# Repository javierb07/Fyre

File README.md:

# Fyre Smartwatch in Development
Smartwatch designed during Summer 2020 at Purdue Milestones

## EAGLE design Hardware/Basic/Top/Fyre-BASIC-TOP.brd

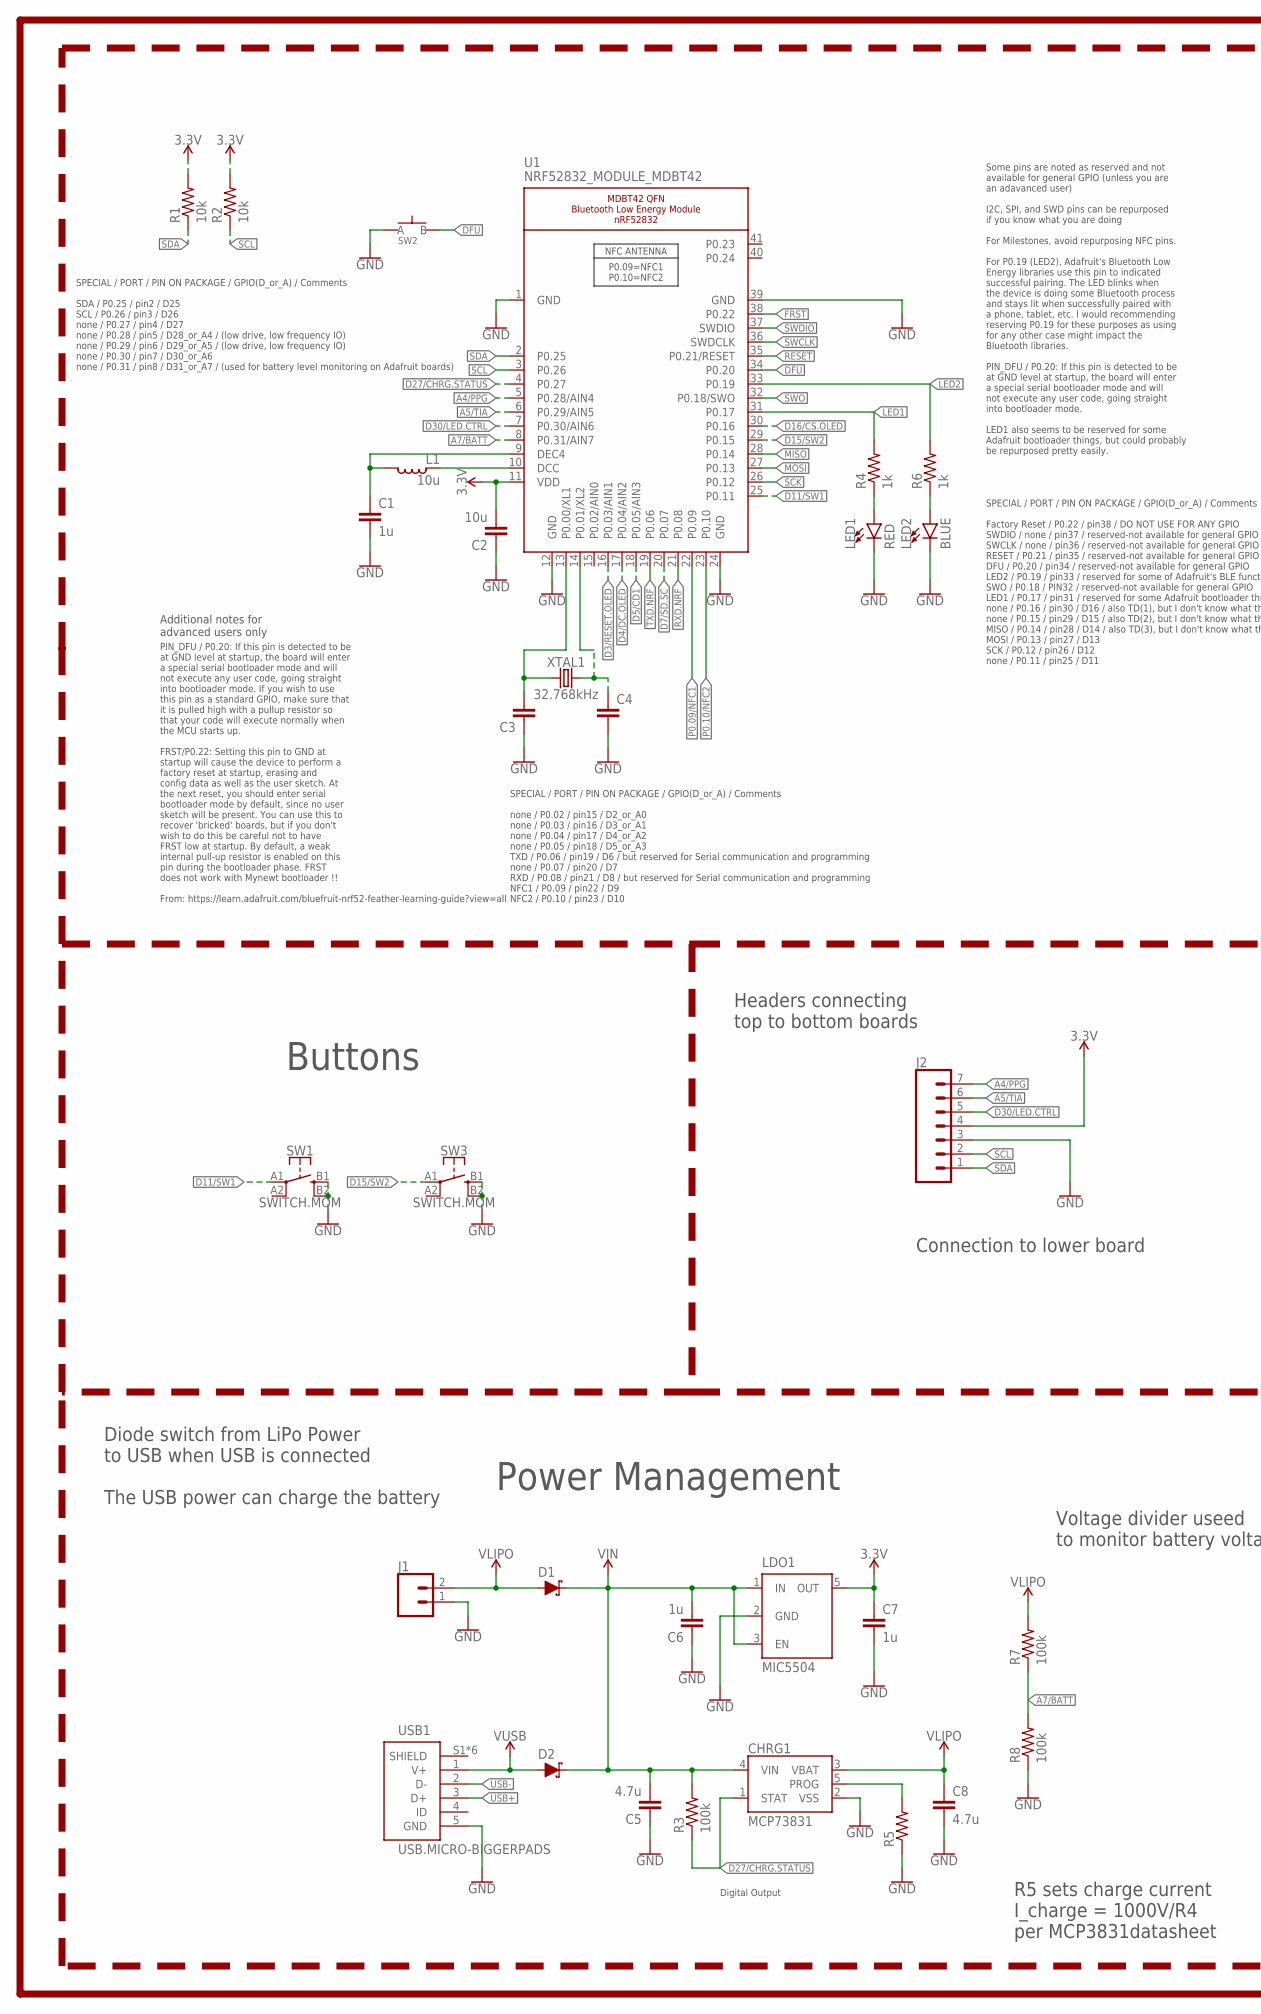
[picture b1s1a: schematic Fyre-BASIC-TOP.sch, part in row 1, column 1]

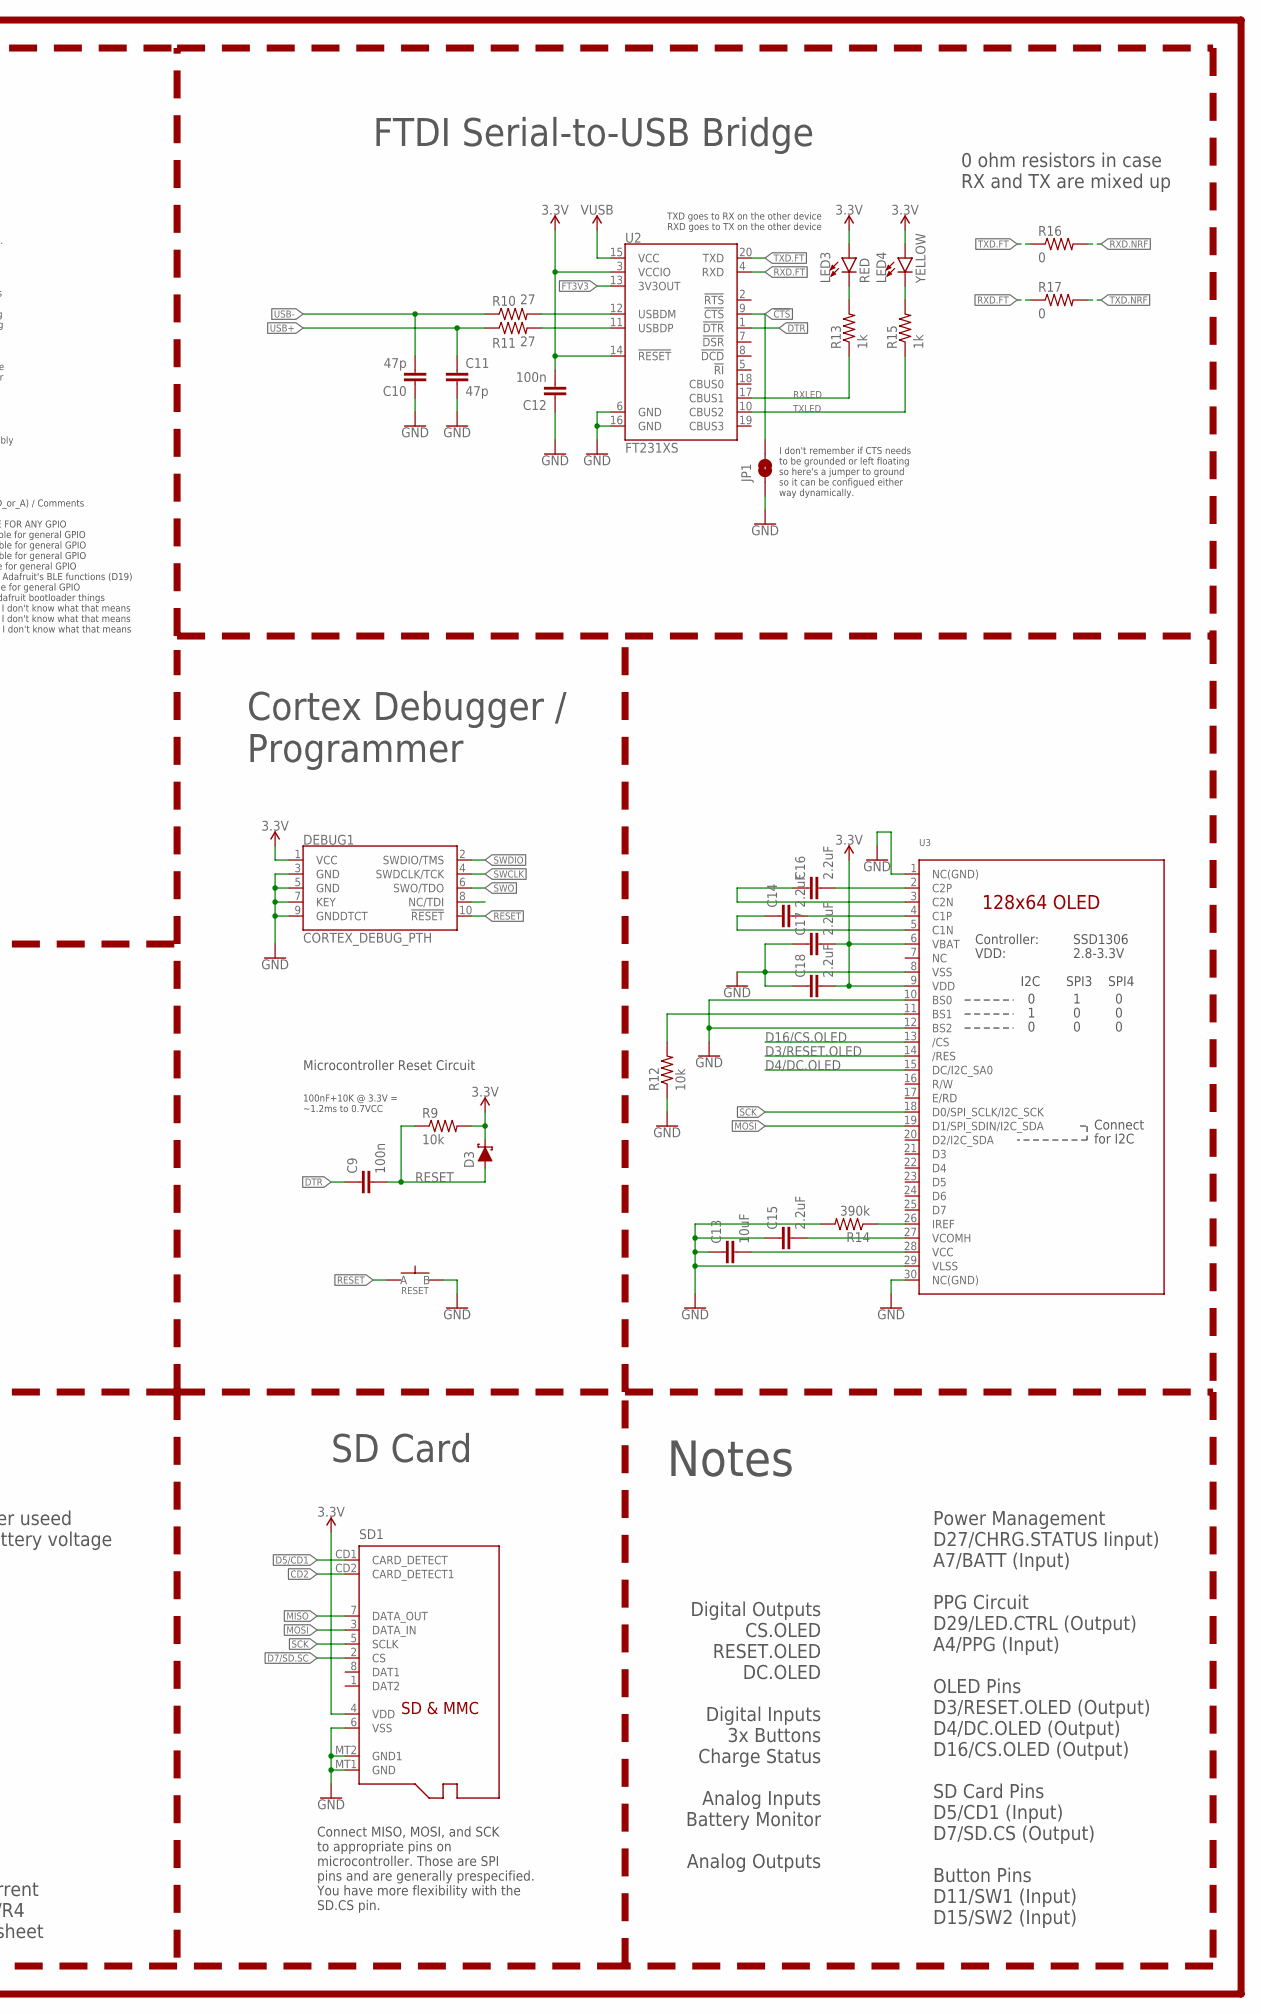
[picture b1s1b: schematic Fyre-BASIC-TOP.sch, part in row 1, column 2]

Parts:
C1, C6, C7: 1u; C0603
C2: 10u; C0805
C3, C4: CAPACITOR0603; C0603
C5, C8: 4.7u; C0603
C9, C12: 100n; C0603
C10, C11: 47p; C0603
C13: 10uF; C0603
C14, C15, C16, C17, C18: 2.2uF; C0402
CHRG1: MCP73831; SOT23-5
D1, D2, D3: SCHOTTKY-USC; USC
DEBUG1: CORTEX_DEBUG_PTH; 2X5-PTH-1.27MM
J1: CONN_02; 1X02
J2: CONN_07-1.27MM; 1X07_1.27MM
JP1: JUMPER-SMT_2_NO_SILK; SMT-JUMPER_2_NO_SILK
L1: 10u; L0603
LDO1: MIC5504; SOT23-5
LED1, LED3: RED; LED-0603
LED2: BLUE; LED-0603
LED4: YELLOW; LED-0603
R1, R2, R9, R12: 10k; R0603
R3, R7, R8: 100k; R0603
R4, R6, R13, R15: 1k; R0603
R5: RESISTOR0603; R0603
R10, R11: 27; R0603
R14: 390k; R0603
R16, R17: 0; R0603
RESET: SPST-PTS830GG140-COPY.1-3; BUTTON-GULLWING
SD1: MICROSD
SW1, SW3: SWITCH.MOM; TACTILE_SWITCH_SMD_6.2MM_TALL
SW2: SPST-PTS830GG140-COPY.1-3; BUTTON-GULLWING
U1: NRF52832_MODULE_MDBT42; BLE_MODULE_RAYTAC_MDBT42
U2: FT231XS; SSOP20_L
U3: DISP_OLED_UG-2864HSWEG01-NO-WRAPAROUND; UG-2864HSWEG01_0.96IN_NO-WRAPAROUND
USB1: USB.MICRO-BIGGERPADS; USB-MICRO-01.BIGGERPADS
XTAL1: 32.768kHz; 2-SMD.NOLEAD.2.0MMTO1.2MM

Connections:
3.3V: C2.2, C7.1, C12.2, C17.2, C18.2, D3.- (C), DEBUG1.1 (VCC), J2.4, LDO1.5 (OUT), LED3.A, LED4.A, R1.2, R2.2, R9.2, SD1.4 (VDD), U1.11 (VDD), U2.3 (VCCIO), U2.14 (!RESET), U3.6 (VBAT), U3.9 (VDD)
!CTS: JP1.2, U2.9 (!CTS)
A4/PPG: J2.7, U1.5 (P0.28/AIN4)
A5/TIA: J2.6, U1.6 (P0.29/AIN5)
A7/BATT: R7.1, R8.2, U1.8 (P0.31/AIN7)
CD2: SD1.CD2 (CARD_DETECT1)
D3/RESET.OLED: U1.16 (P0.03/AIN1), U3.14 (/RES)
D4/DC.OLED: U1.17 (P0.04/AIN2), U3.15 (DC/I2C_SA0)
D5/CD1: SD1.CD1 (CARD_DETECT), U1.18 (P0.05/AIN3)
D7/SD.SC: SD1.2 (CS), U1.20 (P0.07)
D11/SW1: SW1.A1 (1), U1.25 (P0.11)
D15/SW2: SW3.A1 (1), U1.29 (P0.15)
D16/CS.OLED: U1.30 (P0.16), U3.13 (/CS)
D27/CHRG.STATUS: CHRG1.1 (STAT), R3.1, U1.4 (P0.27)
D30/LED.CTRL: J2.5, U1.7 (P0.30/AIN6)
DFU: SW2.3 (B), U1.34 (P0.20)
DTR: C9.1, U2.1 (!DTR)
FRST: U1.38 (P0.22)
FT3V3: U2.13 (3V3OUT)
GND: C1.2, C2.1, C3.1, C4.2, C5.1, C6.1, C7.2, C8.2, C10.1, C11.2, C12.1, C13.1, C15.1, C17.1, C18.1, CHRG1.2 (VSS), DEBUG1.3 (GND), DEBUG1.5 (GND), DEBUG1.7 (KEY), DEBUG1.9 (GNDDTCT), J1.1, J2.3, JP1.1, LDO1.2 (GND), LED1.C, LED2.C, R5.1, R8.1, R12.1, R14.2, RESET.3 (B), SD1.6 (VSS), SD1.MT1 (GND), SD1.MT2 (GND1), SW1.B1 (3), SW1.B2 (4), SW2.1 (A), SW3.B1 (3), SW3.B2 (4), U1.1 (GND), U1.12 (GND), U1.24 (GND), U1.39 (GND), U2.6 (GND), U2.16 (GND), U3.1 (NC(GND)), U3.8 (VSS), U3.10 (BS0), U3.12 (BS2), U3.29 (VLSS), U3.30 (NC(GND)), USB1.5 (GND)
LED1: R4.2, U1.31 (P0.17)
LED2: R6.2, U1.33 (P0.19)
MISO: SD1.7 (DATA_OUT), U1.28 (P0.14)
MOSI: SD1.3 (DATA_IN), U1.27 (P0.13), U3.19 (D1/SPI_SDIN/I2C_SDA)
unnamed: R12.2, U3.11 (BS1)
unnamed: R14.1, U3.26 (IREF)
unnamed: C16.2, U3.2 (C2P)
unnamed: C3.2, U1.13 (P0.00/XL1), XTAL1.P$1 (1)
unnamed: C16.1, U3.3 (C2N)
unnamed: C14.2, U3.4 (C1P)
unnamed: C14.1, U3.5 (C1N)
unnamed: LED1.A, R4.1
unnamed: LED2.A, R6.1
unnamed: L1.1, U1.10 (DCC)
unnamed: C1.1, L1.2, U1.9 (DEC4)
unnamed: C13.2, U3.28 (VCC)
unnamed: C15.2, U3.27 (VCOMH)
unnamed: C4.1, U1.14 (P0.01/XL2), XTAL1.P$2 (2)
unnamed: CHRG1.5 (PROG), R5.2
unnamed: R10.2, U2.12 (USBDM)
unnamed: R11.2, U2.11 (USBDP)
unnamed: LED3.C, R13.2
unnamed: LED4.C, R15.2
P0.09/NFC1: U1.22 (P0.09)
P0.10/NFC2: U1.23 (P0.10)
RESET: C9.2, D3.+ (A), DEBUG1.10 (!RESET), R9.1, RESET.1 (A), U1.35 (P0.21/RESET)
RXD.FT: R17.1, U2.4 (RXD)
RXD.NRF: R16.2, U1.21 (P0.08)
RXLED: R13.1, U2.17 (CBUS1)
SCK: SD1.5 (SCLK), U1.26 (P0.12), U3.18 (D0/SPI_SCLK/I2C_SCK)
SCL: J2.2, R2.1, U1.3 (P0.26)
SDA: J2.1, R1.1, U1.2 (P0.25)
SWCLK: DEBUG1.4 (SWDCLK/TCK), U1.36 (SWDCLK)
SWDIO: DEBUG1.2 (SWDIO/TMS), U1.37 (SWDIO)
SWO: DEBUG1.6 (SWO/TDO), U1.32 (P0.18/SWO)
TXD.FT: R16.1, U2.20 (TXD)
TXD.NRF: R17.2, U1.19 (P0.06)
TXLED: R15.1, U2.10 (CBUS2)
USB+: C11.1, R11.1, USB1.3 (D+)
USB-: C10.2, R10.1, USB1.2 (D-)
VIN: C5.2, C6.2, CHRG1.4 (VIN), D1.- (C), D2.- (C), LDO1.1 (IN), LDO1.3 (EN), R3.2
VLIPO: C8.1, CHRG1.3 (VBAT), D1.+ (A), J1.2, R7.2
V_USB: D2.+ (A), U2.15 (VCC), USB1.1 (V+)

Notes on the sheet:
Microcontroller Reset Circuit
100nF+10K @ 3.3V = ~1.2ms to 0.7VCC
SPECIAL / PORT / PIN ON PACKAGE / GPIO(D_or_A) / Comments SDA / P0.25 / pin2 / D25 SCL / P0.26 / pin3 / D26 none / P0.27 / pin4 / D27 none / P0.28 / pin5 / D28_or_A4 / (low drive, low frequency IO) none / P0.29 / pin6 / D29_or_A5 / (low drive, low frequency IO) none / P0.30 / pin7 / D30_or_A6 none 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
SPECIAL / PORT / PIN ON PACKAGE / GPIO(D_or_A) / Comments none / P0.02 / pin15 / D2_or_A0 none / P0.03 / pin16 / D3_or_A1 none / P0.04 / pin17 / D4_or_A2 none / P0.05 / pin18 / D5_or_A3 TXD / P0.06 / pin19 / D6 / but reserved for Serial communication and programming none / P0.07 / pin20 / D7 RXD / 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
SPECIAL / PORT / PIN ON PACKAGE / GPIO(D_or_A) / Comments Factory Reset / P0.22 / pin38 / DO NOT USE FOR ANY GPIO SWDIO / none / pin37 / reserved-not available for general GPIO SWCLK / none / pin36 / reserved-not available for general GPIO RESET / P0.21 / pin35 / reserved-not available for general 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
Some pins are noted as reserved and not available for general GPIO (unless you are an adavanced user) I2C, SPI, and SWD pins can be repurposed if you know what you are doing For Milestones, avoid repurposing NFC pins. For P0.19 (LED2), Adafruit's Bluetooth Low Energy libraries use this pin to indic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
PIN_DFU / P0.20: If this pin is detected to be at GND level at startup, the board will enter a special serial bootloader mode and will not execute any user code, going straight into bootloader mode. If you wish to use this pin as a standard GPIO, make sure that it is pulled high with a pullup resis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
Additional notes for advanced users only
Connect MISO, MOSI, and SCK to appropriate pins on microcontroller. Those are SPI pins and are generally prespecified. You have more flexibility with the SD.CS pin.
SD Card
Power Management
Buttons
Cortex Debugger / Programmer
Digital Outputs CS.OLED RESET.OLED DC.OLED Digital Inputs 3x Buttons Charge Status Analog Inputs Battery Monitor Analog Outputs
TXD goes to RX on the other device RXD goes to TX on the other device
I don't remember if CTS needs to be grounded or left floating so here's a jumper to ground so it can be configued either way dynamically.
FTDI Serial-to-USB Bridge
Notes
Digital Output
Power Management D27/CHRG.STATUS Iinput) A7/BATT (Input) PPG Circuit D29/LED.CTRL (Output) A4/PPG (Input) OLED Pins D3/RESET.OLED (Output) D4/DC.OLED (Output) D16/CS.OLED (Output) SD Card Pins D5/CD1 (Input) D7/SD.CS (Output) Button Pins D11/SW1 (Input) D15/SW2 (Input)
Connection to lower board
Diode switch from LiPo Power to USB when USB is connected The USB power can charge the battery
R5 sets charge current I_charge = 1000V/R4 per MCP3831datasheet
Voltage divider useed to monitor battery voltage
Headers connecting top to bottom boards
0 ohm resistors in case RX and TX are mixed up

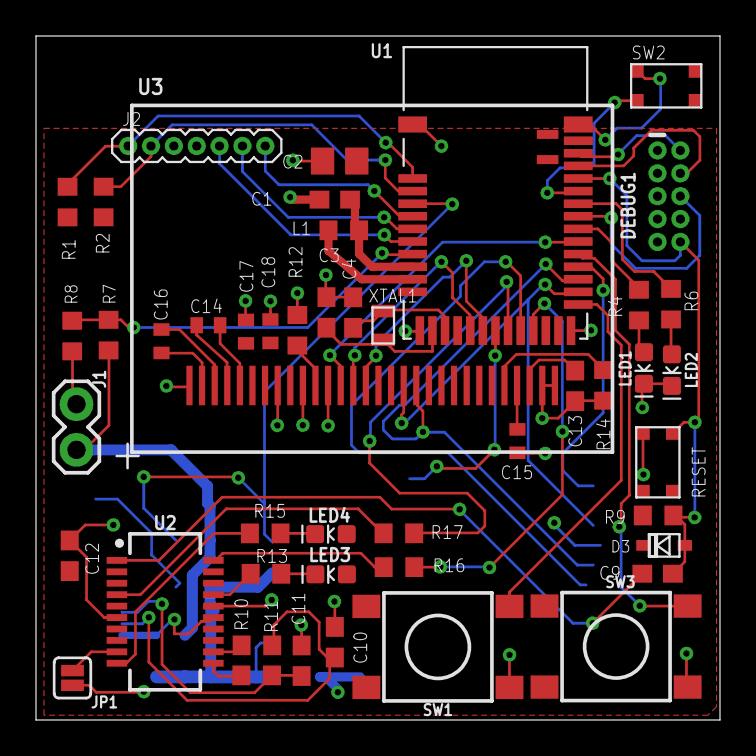
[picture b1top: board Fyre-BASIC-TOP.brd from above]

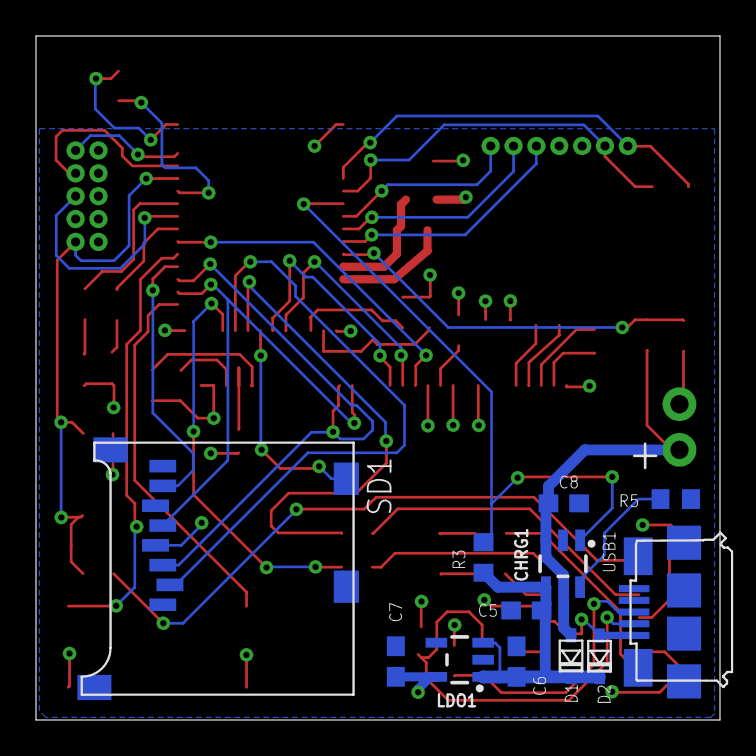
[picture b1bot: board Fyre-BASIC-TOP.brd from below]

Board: 2 copper layers, 38.0 x 38.0 mm, 59 parts (12 on the bottom side), 58 nets.

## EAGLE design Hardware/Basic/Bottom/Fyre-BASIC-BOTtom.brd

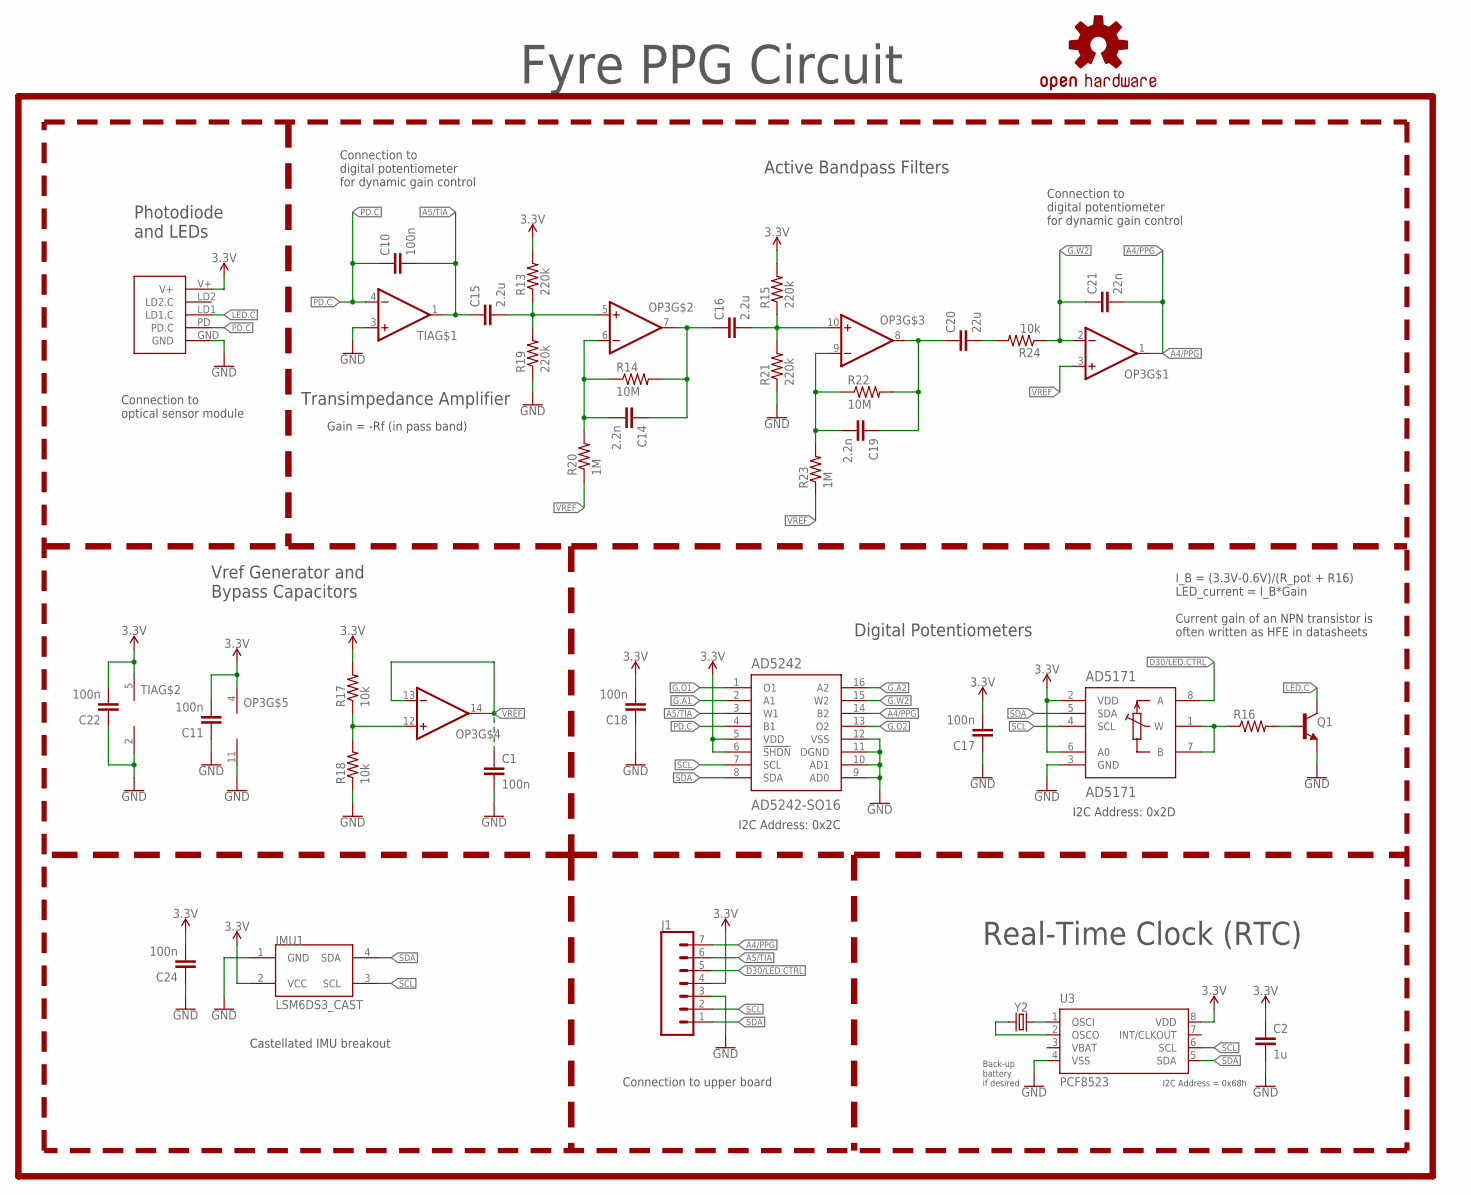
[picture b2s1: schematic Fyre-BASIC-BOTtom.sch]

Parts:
AD5171: AD5171; SOT-23-8
AD5242: AD5242-SO16; SO16
C1, C10, C11, C17, C18, C22, C24: 100n; C0603
C2: 1u; C0603
C14, C19: 2.2n; C0603
C15, C16: 2.2u; C0603
C20: 22u; C0603
C21: 22n; C0603
IMU1: LSM6DS3_CAST
J1: CONN_07-1.27MM; 1X07_1.27MM
LOGO1: REVISION.A; REV.A
LOGO2: OSHW-LOGOS; OSHW-LOGO-S
OP3: OP-QUAD-SO14; SO14
Q1: NPN-GENERIC; SOT23-3
R13, R15, R19, R21: 220k; R0603
R14, R22: 10M; R0603
R16: RESISTOR0603; R0603
R17, R18: 10k; R0402
R20, R23: 1M; R0603
R24: 10k; R0603
TIA: OP-SINGLEOT; SOT23-5
U3: PCF8523; SO8; DIGIKEY 568-5306-1-ND
U$3: PPG.MODULE.2
Y2: 32.7680kHz; 2-SMD.NOLEAD.2.0MMTO1.2MM

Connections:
3.3V: AD5171.2 (VDD), AD5171.6 (A0), AD5242.5 (VDD), AD5242.6 (!SHDN), C2.1, C11.2, C17.2, C18.2, C22.2, C24.2, IMU1.2 (VCC), J1.4, OP3.4 (V+), R13.2, R15.2, R17.2, TIA.5 (V+), U3.8 (VDD), U$3.V+
A4/PPG: AD5242.14 (B2), C21.2, J1.7, OP3.1 (OUT)
A5/TIA: AD5242.3 (W1), C10.2, C15.1, J1.6, TIA.1 (OUT)
D30/LED.CTRL: AD5171.8 (A), J1.5
G.A1: AD5242.2 (A1)
G.A2: AD5242.16 (A2)
G.O1: AD5242.1 (O1)
G.O2: AD5242.13 (O2)
G.W2: AD5242.15 (W2), C21.1, OP3.2 (-IN), R24.1
GND: AD5171.3 (GND), AD5242.9 (AD0), AD5242.10 (AD1), AD5242.11 (DGND), AD5242.12 (VSS), C1.2, C2.2, C11.1, C17.1, C18.1, C22.1, C24.1, IMU1.1 (GND), J1.3, OP3.11 (V-), Q1.2 (E), R18.1, R19.1, R21.1, TIA.2 (V-), TIA.3 (+IN), U3.4 (VSS), U$3.GND
LED.C: Q1.3 (C), U$3.LD1 (LD1.C)
unnamed: U3.1 (OSCI), Y2.P$2 (2)
unnamed: U3.2 (OSCO), Y2.P$1 (1)
unnamed: Q1.1 (B), R16.2
unnamed: AD5171.1 (W), AD5171.7 (B), R16.1
unnamed: OP3.12 (+IN), R17.1, R18.2
unnamed: C15.2, OP3.5 (+IN), R13.1, R19.2
unnamed: C14.2, OP3.6 (-IN), R14.1, R20.2
unnamed: C14.1, C16.1, OP3.7 (OUT), R14.2
unnamed: C16.2, OP3.10 (+IN), R15.1, R21.2
unnamed: C19.2, OP3.9 (-IN), R22.1, R23.2
unnamed: C19.1, C20.1, OP3.8 (OUT), R22.2
unnamed: C20.2, R24.2
PD.C: AD5242.4 (B1), C10.1, TIA.4 (-IN), U$3.PD (PD.C)
SCL: AD5171.4 (SCL), AD5242.7 (SCL), IMU1.3 (SCL), J1.2, U3.6 (SCL)
SDA: AD5171.5 (SDA), AD5242.8 (SDA), IMU1.4 (SDA), J1.1, U3.5 (SDA)
VBAT: U3.3 (VBAT)
VREF: C1.1, OP3.3 (+IN), OP3.13 (-IN), OP3.14 (OUT), R20.1, R23.1

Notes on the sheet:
Photodiode and LEDs
Active Bandpass Filters
Digital Potentiometers
Transimpedance Amplifier
I2C Address: 0x2C
I2C Address: 0x2D
Connection to optical sensor module
Connection to digital potentiometer for dynamic gain control
Connection to upper board
Castellated IMU breakout
Vref Generator and Bypass Capacitors
Fyre PPG Circuit
Real-Time Clock (RTC)
I2C Address = 0x68h
Back-up battery if desired
I_B = (3.3V-0.6V)/(R_pot + R16) LED_current = I_B*Gain Current gain of an NPN transistor is often written as HFE in datasheets
Gain = -Rf (in pass band)

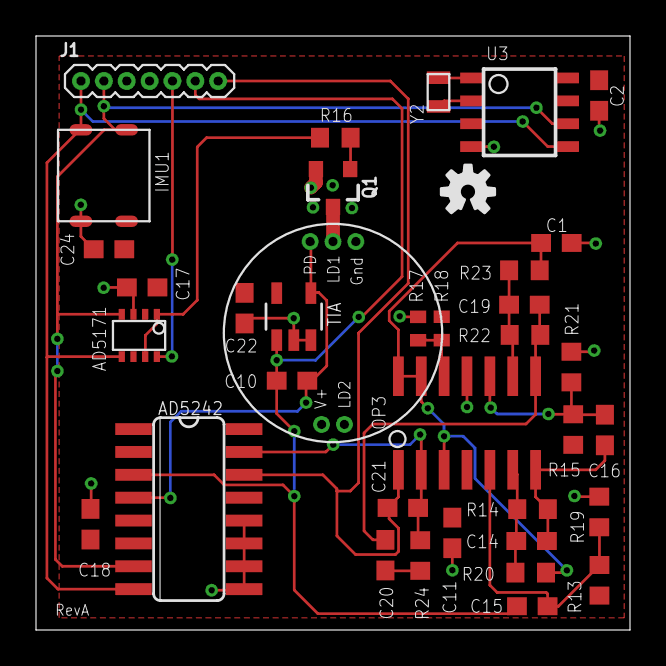
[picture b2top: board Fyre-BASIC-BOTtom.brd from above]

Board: 2 copper layers, 33.0 x 33.0 mm, 38 parts (0 on the bottom side), 23 nets.

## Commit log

2020-06-30 Added document with list of features
2020-06-30 Added list of features
2020-06-30 Added gitignore
2020-07-01 Created Repo Structure
2020-07-01 Removed unnecesary file
2020-07-07 Added more features
2020-07-07 Added sch files
2020-07-09 Worked on the top board
2020-07-14 Added bottom and PPG boards
2020-07-19 Completed the top board
2020-07-21 Small changes
2020-07-28 Added the PPG library
2020-07-29 Included PPG as an Arduino library
2020-08-12 Worked on firmware
